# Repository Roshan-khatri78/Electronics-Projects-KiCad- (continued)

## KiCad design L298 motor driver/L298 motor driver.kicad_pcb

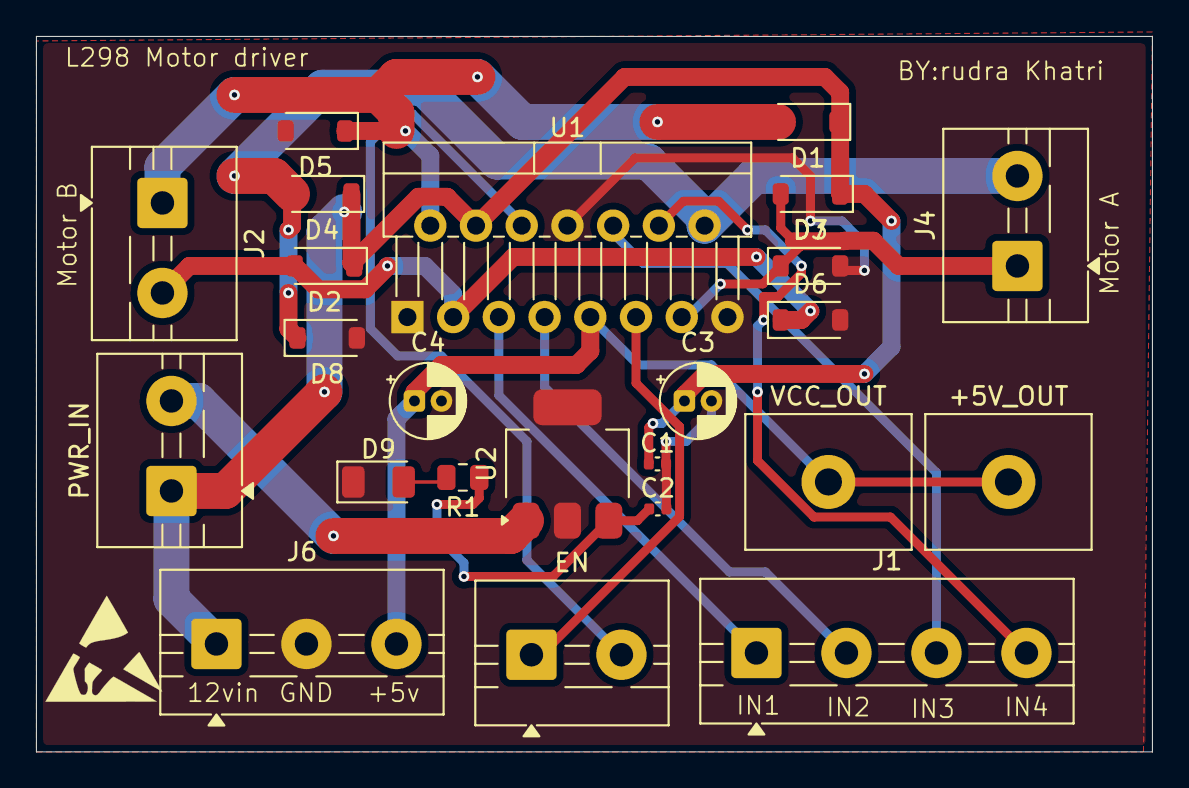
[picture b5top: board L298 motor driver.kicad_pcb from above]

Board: 2 copper layers, 62.0 x 39.8 mm, 24 parts (0 on the bottom side), 16 nets.

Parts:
+5V_OUT : Screw_Terminal_01x01; TerminalBlock_MetzConnect_360271_1x01_Horizontal_ScrewM3.0_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
C1, C2: C_Polarized; C_0402_1005Metric
C3, C4: C_Polarized; CP_Radial_D4.0mm_P1.50mm
D1, D2, D3, D4, D5, D6, D7, D8: 1N4148W; D_SOD-123
D9: LED; LED_1206_3216Metric
EN: EN; TerminalBlock_MaiXu_MX126-5.0-02P_1x02_P5.00mm
J1: INpins; TerminalBlock_MaiXu_MX126-5.0-04P_1x04_P5.00mm
J2: MtrA; TerminalBlock_MaiXu_MX126-5.0-02P_1x02_P5.00mm
J4: MtrB; TerminalBlock_MaiXu_MX126-5.0-02P_1x02_P5.00mm
J6: Screw_Terminal_01x03; TerminalBlock_MaiXu_MX126-5.0-03P_1x03_P5.00mm
PWR_IN: EN; TerminalBlock_MaiXu_MX126-5.0-02P_1x02_P5.00mm
R1: R; R_0805_2012Metric
U1: L298N; TO-220-15_P2.54x5.08mm_StaggerOdd_Lead4.58mm_Vertical
U2: UA78M05QDCYRQ1; SOT-223-3_TabPin2
VCC_OUT: Screw_Terminal_01x01; TerminalBlock_MetzConnect_360271_1x01_Horizontal_ScrewM3.0_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

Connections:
/+5V: +5V_OUT.1 (Pin_1_1), C4.1, J6.3, U1.9 (Vss), VCC_OUT.1 (Pin_1_1)
/VCC: C1.1, C3.1, D1.1 (K), D2.1 (K), D3.1 (K), D4.1 (K), J6.1, PWR_IN.1, U1.4 (Vs)
GND: C1.2, C2.2, C3.2, C4.2, D5.2 (A), D6.2 (A), D7.2 (A), D8.2 (A), D9.1 (K), J6.2, U1.1 (SENSE_A), U1.8 (GND), U1.15 (SENSE_B), U2.2 (GND)
unnamed: D1.2 (A), D5.1 (K), J2.1, U1.2 (OUT1)
unnamed: D2.2 (A), D6.1 (K), J2.2, U1.3 (OUT2)
unnamed: D3.2 (A), D7.1 (K), J4.1, U1.13 (OUT3)
unnamed: D4.2 (A), D8.1 (K), J4.2, U1.14 (OUT4)
unnamed: D9.2 (A), R1.2
unnamed: J1.1, U1.5 (IN1)
unnamed: J1.2, U1.7 (IN2)
unnamed: J1.3, U1.10 (IN3)
unnamed: J1.4, U1.12 (IN4)
unnamed: EN.1, U1.11 (EnB)
unnamed: EN.2, U1.6 (EnA)
unnamed: PWR_IN.2, U2.1 (IN)
unnamed: C2.1, R1.1, U2.3 (OUT)

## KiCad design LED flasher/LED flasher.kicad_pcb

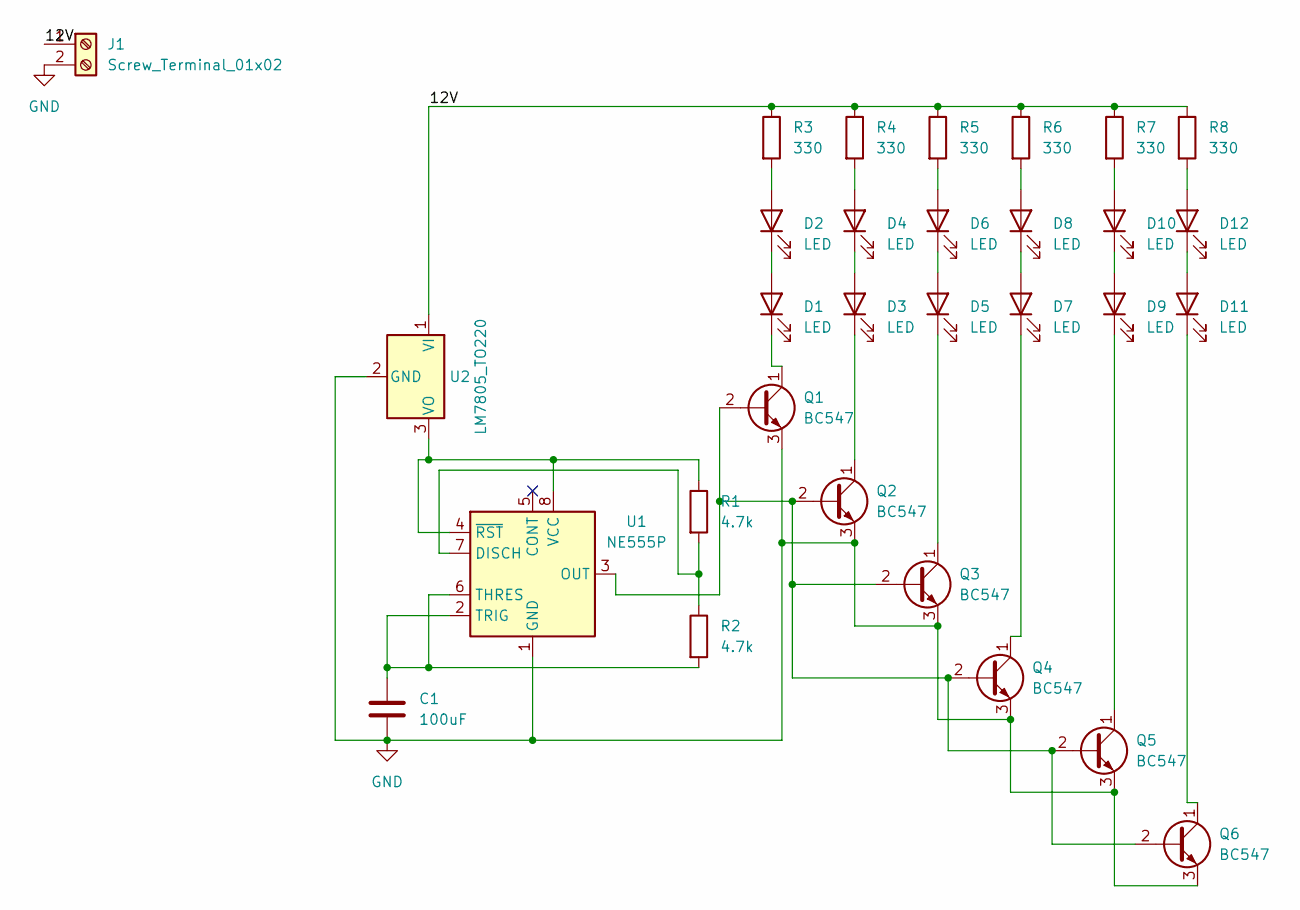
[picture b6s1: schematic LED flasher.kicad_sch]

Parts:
C1: 100uF; CP_EIA-6032-15_Kemet-U_HandSolder
D1, D2, D3, D4, D5, D6, D7, D8, D9, D10, D11, D12: LED; LED_D5.0mm
J1: Screw_Terminal_01x02; TerminalBlock_MaiXu_MX126-5.0-02P_1x02_P5.00mm
Q1, Q2, Q3, Q4, Q5, Q6: BC547; TO-92_Inline
R1, R2: 4.7k; R_Axial_DIN0204_L3.6mm_D1.6mm_P2.54mm_Vertical
R3, R4, R5, R6, R7, R8: 330; R_Axial_DIN0204_L3.6mm_D1.6mm_P2.54mm_Vertical
U1: NE555P; DIP-8_W7.62mm
U2: LM7805_TO220; TO-220-3_Vertical

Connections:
/12V: J1.1, R3.1, R4.1, R5.1, R6.1, R7.1, R8.1, U2.1 (VI)
GND: C1.2, J1.2, Q1.3 (E), Q2.3 (E), Q3.3 (E), Q4.3 (E), Q5.3 (E), Q6.3 (E), U1.1 (GND), U2.2 (GND)
unnamed: D1.2 (A), D2.1 (K)
unnamed: D1.1 (K), Q1.1 (C)
unnamed: D2.2 (A), R3.2
unnamed: D3.2 (A), D4.1 (K)
unnamed: D3.1 (K), Q2.1 (C)
unnamed: D4.2 (A), R4.2
unnamed: D5.2 (A), D6.1 (K)
unnamed: D5.1 (K), Q3.1 (C)
unnamed: D6.2 (A), R5.2
unnamed: D7.2 (A), D8.1 (K)
unnamed: D7.1 (K), Q4.1 (C)
unnamed: D8.2 (A), R6.2
unnamed: D9.1 (K), Q5.1 (C)
unnamed: D10.2 (A), R7.2
unnamed: D9.2 (A), D10.1 (K)
unnamed: D11.2 (A), D12.1 (K)
unnamed: D11.1 (K), Q6.1 (C)
unnamed: D12.2 (A), R8.2
unnamed: Q1.2 (B), Q2.2 (B), Q3.2 (B), Q4.2 (B), Q5.2 (B), Q6.2 (B), U1.3 (OUT)
unnamed: R1.2, R2.1, U1.7 (DISCH)
unnamed: C1.1, R2.2, U1.2 (TRIG), U1.6 (THRES)
unnamed: R1.1, U1.4 (~RST), U1.8 (VCC), U2.3 (VO)

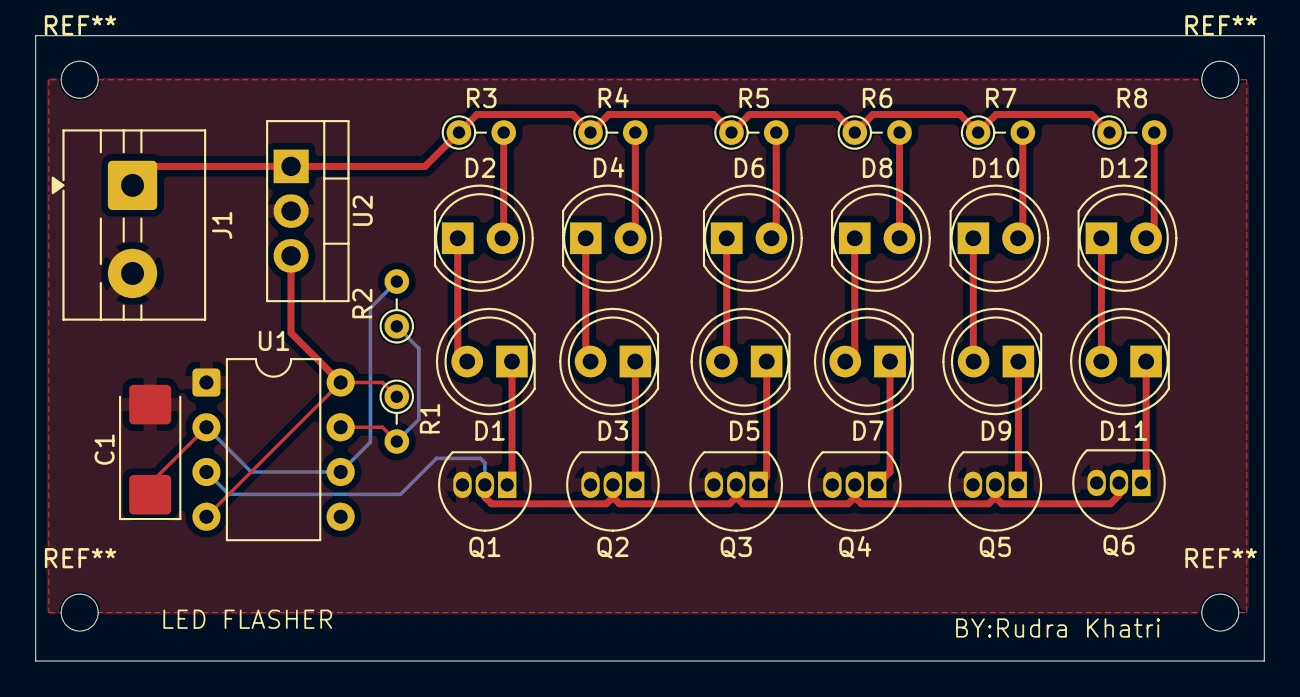
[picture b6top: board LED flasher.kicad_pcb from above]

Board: 4 copper layers, 69.8 x 35.5 mm, 30 parts (0 on the bottom side), 24 nets.

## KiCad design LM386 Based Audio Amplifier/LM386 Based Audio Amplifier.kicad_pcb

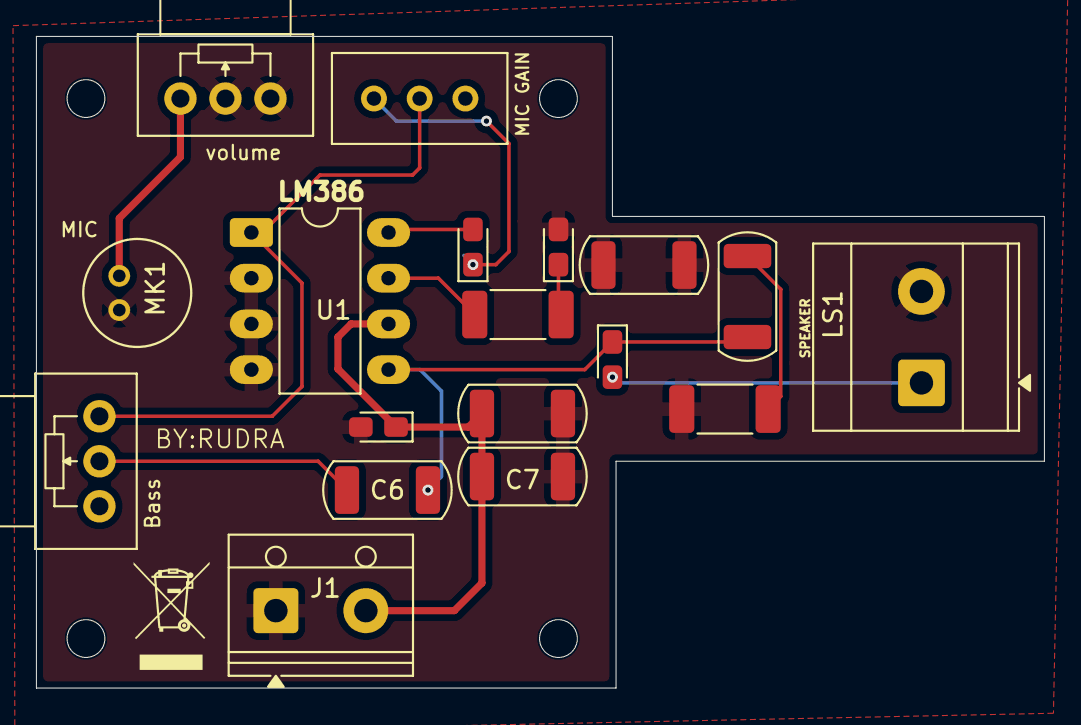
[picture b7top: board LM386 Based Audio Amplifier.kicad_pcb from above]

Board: 2 copper layers, 56.0 x 36.2 mm, 18 parts (0 on the bottom side), 12 nets.

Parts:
Bass: 10k; Potentiometer_Alps_RK09Y11_Single_Horizontal
C1: 1000uf/15v; CP_EIA-2012-12_Kemet-R_HandSolder
C2: 100uf/15v; CP_EIA-2012-12_Kemet-R_HandSolder
C3, C4: 10uf/15v; CP_EIA-2012-12_Kemet-R_HandSolder
C5: 0.1uF; C_2010_5025Metric
C6: 0.033uf; C_2010_5025Metric
C7, C8, C9: 0.1uf; C_2010_5025Metric
J1: Screw_Terminal_01x02; TerminalBlock_RND_205-00012_1x02_P5.00mm_Horizontal
LS1: Speaker; TerminalBlock_Phoenix_MKDS-3-2-5.08_1x02_P5.08mm_Horizontal
MIC GAIN: 10k; Potentiometer_Bourns_3296W_Vertical
MK1: Microphone; CUI_CMC-5044PF-A
R2, R3: 10k; R_2010_5025Metric_Pad1.40x2.65mm_HandSolder
U1: LM386; DIP-8_W7.62mm_LongPads
volume: 10k; Potentiometer_Alps_RK09Y11_Single_Horizontal

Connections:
/+v: C2.1, C7.2, C8.2, J1.2, U1.6 (V+)
/OUT: MK1.2 (+), volume.3
GND: C2.2, C4.2, C7.1, C8.1, C9.1, C9.2, J1.1, LS1.2, MK1.1 (-), R2.1, U1.2 (-), U1.3 (+), U1.4 (GND), volume.1, volume.2
unnamed: C1.1, C5.1, C6.1, U1.5
unnamed: C1.2, LS1.1
unnamed: C3.1, MIC GAIN.1
unnamed: C3.2, U1.8 (GAIN)
unnamed: C4.1, R3.2
unnamed: C5.2, R2.2
unnamed: Bass.2, C6.2
unnamed: Bass.1, MIC GAIN.2, U1.1 (GAIN)
unnamed: R3.1, U1.7 (BYPASS)

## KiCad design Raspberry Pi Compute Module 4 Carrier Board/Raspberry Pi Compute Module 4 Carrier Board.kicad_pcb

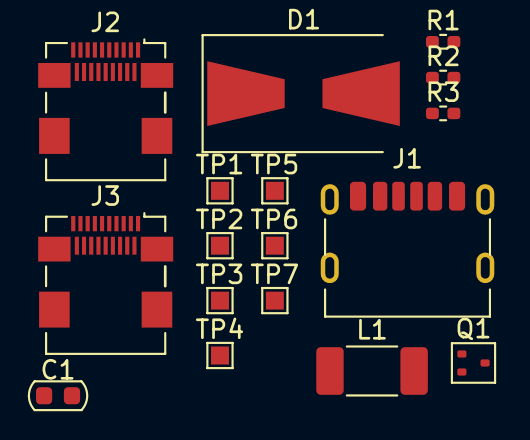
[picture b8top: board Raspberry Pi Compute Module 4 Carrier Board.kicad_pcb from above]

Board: 2 copper layers, 17 parts (0 on the bottom side), 3 nets, no tracks yet.

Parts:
C1: 10u; C_0603_1608Metric
D1: D_Zener; D_SMB-SMC_Universal_Handsoldering
J1: USB_C_Receptacle_USB2.0_14P; USB_C_Receptacle_HRO_TYPE-C-31-M-17
J2, J3: HDMI_B; HDMI_Micro-D_Molex_46765-0xxx
L1: L; L_2010_5025Metric_Pad1.52x2.65mm_HandSolder
Q1: DMG1012T; SOT-523
R1, R2: 5K1; R_0402_1005Metric_Pad0.72x0.64mm_HandSolder
R3: 10R; R_0402_1005Metric_Pad0.72x0.64mm_HandSolder
TP1, TP2, TP3, TP4, TP5, TP6, TP7: TestPoint_Alt; TestPoint_Pad_1.0x1.0mm

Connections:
/5V: D1.1 (K), J1.A9 (VBUS), J1.B9 (VBUS), TP1.1 (1_1), TP2.1 (1_1), TP3.1 (1_1)
/USB_CC: J1.A5 (CC1), J1.B5 (CC2), R1.1, R2.1
GND: D1.2 (A), J1.A12 (GND), J1.B12 (GND), J1.SH (SHIELD), J2.SH, J3.SH, R1.2, TP4.1 (1_1), TP5.1 (1_1), TP6.1 (1_1), TP7.1 (1_1)
